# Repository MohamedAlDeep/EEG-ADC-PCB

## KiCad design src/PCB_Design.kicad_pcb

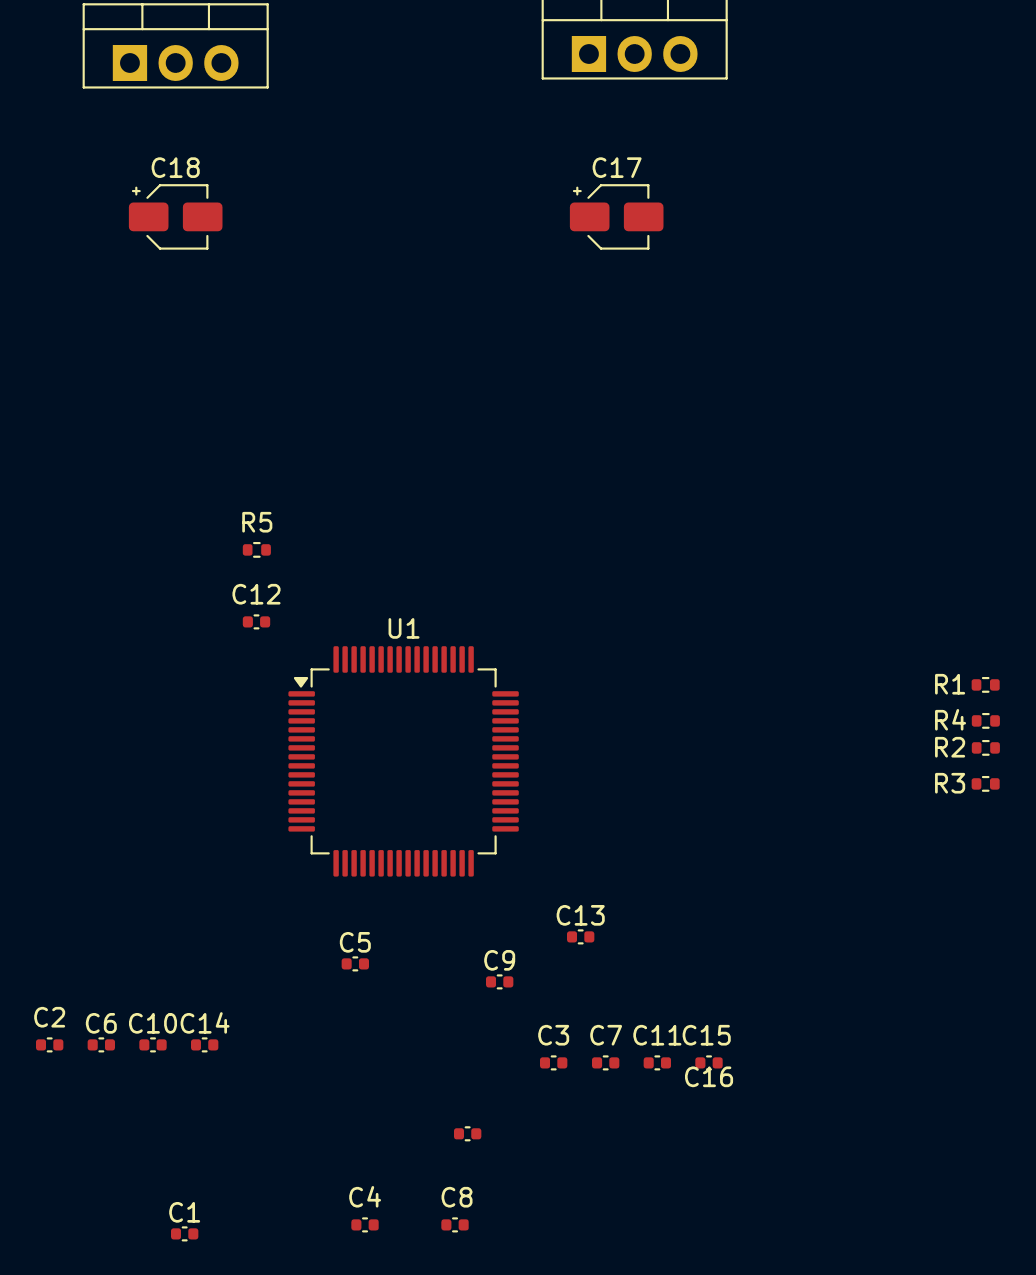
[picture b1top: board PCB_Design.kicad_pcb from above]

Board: 2 copper layers, 26 parts (0 on the bottom side), 22 nets, no tracks yet.

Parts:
C1, C4: 100nF; C_0402_1005Metric
C2, C3, C8, C9, C10, C15, C16: 1μF; C_0402_1005Metric
C5, C6, C11, C13: 0.1μF; C_0402_1005Metric
C7: 100μF; C_0402_1005Metric
C12: 1nF; C_0402_1005Metric
C14: 10μF; C_0402_1005Metric
C17, C18: 10μF; CP_Elec_3x5.4
R1, R2, R3, R4: 10-kΩ; R_0402_1005Metric
R5: 1-MΩ; R_0402_1005Metric
U1: ADS1299xPAG; TQFP-64_10x10mm_P0.5mm
U2: LM7805_TO220; TO-220-3_Vertical
U3: LD1117V33; TO-220-3_Vertical

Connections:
+3.7V: C18.2, U3.3 (VI)
+7.5V: C17.2, U2.1 (VI)
/Regulator_3.3V: C6.2, C16.1, U1.48 (DVDD), U1.50 (DVDD), U3.2 (VO)
/Regulator_5V: C3.1, C5.2, U1.19 (AVDD), U1.21 (AVDD), U1.22 (AVDD), U1.54 (AVDD1), U1.56 (AVDD), U1.59 (AVDD), U2.3 (VO)
AGND: C1.2, C2.2, C3.2, C4.1, C5.1, C6.1, C15.2, C16.2, C17.1, C18.1, U1.31 (RESV1), U1.41 (DAISY_IN), U1.60 (BIASREF), U1.64 (RESERVED), U2.2 (GND), U3.1 (GND)
AVDD: C2.1, C15.1
AVSS: C7.1, C8.1, C9.1, C10.1, C11.2, C13.2, C14.1, U1.20 (AVSS), U1.23 (AVSS), U1.24 (VREFP), U1.32 (AVSS), U1.53 (AVSS1), U1.57 (AVSS), U1.58 (AVSS)
BIAS_DRV: C12.2, R5.2
DGND: U1.33 (DGND), U1.49 (DGND), U1.51 (DGND)
DVDD: C1.1, C4.2, U1.35 (~PWDN), U1.52 (CLKSEL)
GND: R1.2, R2.2, R3.2, R4.2
IN1P: U1.15 (IN1N), U1.16 (IN1P)
unnamed: C12.1, R5.1, U1.62 (BIASIN), U1.63 (BIASOUT)
unnamed: R3.1, U1.42 (GPIO1)
unnamed: R2.1, U1.44 (GPIO2)
unnamed: R4.1, U1.45 (GPIO3)
unnamed: R1.1, U1.46 (GPIO4)
unnamed: C7.2, U1.28 (VCAP1)
unnamed: C8.2, U1.30 (VCAP2)
unnamed: C9.2, C11.1, U1.55 (VCAP3)
unnamed: C10.2, U1.26 (VCAP4)
unnamed: C13.1, C14.2, U1.25 (VREFN)

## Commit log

2025-08-14 init
2025-08-14 configured the journal
2025-08-15 Schematic
2025-08-16 Reverse Polarity Protection
